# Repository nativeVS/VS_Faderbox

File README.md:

# VS_Faderbox

A small Teensy based MIDI Faderbox;  
built around [ttapa's Control Surface Library](https://github.com/tttapa/Control-Surface)

## Overview

This project was born out of the desire of having a small MIDI fader controller to ease in the work with orchestral libraries.
  
The MIDI Channel and Fader Assignment can be changed via MIDI System Exclusive messages (described in more detail below).
I have written a (low quality) program that lets you quickly generate a SysEx file should you wish to avoid doing it the fun way (link below or [here](https://github.com/nativeVS/VS_SysEx_Generator)).
In addition new for version 5 there is an editor software (link below or [here](https://github.com/nativeVS/VS_Faderbox_Editor)) which is a simple Electron built application using WebMIDI, heavily inspired by the nakedboards editor.
  
On the PCB there is the provision to add 4 extra potentiometers with pull down resistors (eg. for external expression pedals or similar);
more info in the DIY Notes section.
  
### Links

* [ttapa's Control Surface Library](https://github.com/tttapa/Control-Surface)
* [SysEx Generator](https://github.com/nativeVS/VS_SysEx_Generator)
* [Editor](https://github.com/nativeVS/VS_Faderbox_Editor)
* [nakedboards](https://nakedboards.org/)

#### Contents of the sub-directories are as follows
* VS_Faderbox - Teensyduino Sketch
* CAD Files - Full KiCad Project directory for PCB & AutoCAD files for physical box.

## SysEx Format

Channel and Fader Reassignment SysEx Format:
```
F0 [id] [id] [id] [dI] [s1] [s2] [cc] [f0] [f1] [f2] [f3] xx F7
```
With manufacturer ID (`[id] [id] [id]`), device id (`[dI]`) and sub ids #1 & #2 (`[s1] [s2]` which correspond to model number and version number for this device);
the Checksum (xx) includes the entire SysEx message (i.e. starting with the device ID) and should add up to `FF` with all preceding elements.
The Device ID is in the normal version fixed to 0x01.
  
Thus the SysEx string for the default assignment is as follows:
```
F0 00 21 57 01 02 05 01 01 0B 15 14 40 F7
```
To request the current Channel and Fader assignment the box responds to the following SysEx:
```
F0 [id] [id] [id] [dI] [s1] [s2] 0x11 xx F7
```
This will trigger the following response:
```
F0 [id] [id] [id] [dI] 0x00 [s2] [cc] [f0] [f1] [f2] [f3] xx F7
```

It will respond to the standard SysEx ID Requests:
```
F0 7E 01 06 01 F7 (device id 01) or
F0 7E 7F 06 01 F7 (ignore device id)
```
SysEx ID Request Reply:
```
F0 7E 01 06 02 [id] [id] [id] 01 01 00 02 00 00 00 05 F7
                              |   | |   | |---------- Software Version No: v5
                              |   | |---- Model Number: 00 02
                              |---- Family Code: 01 01
```
  
## DIY Notes

todo: add more detail
  
This sketch was designed for a Teensy LC and might not work correctly on lower spec boards.
  
#### Expansion Notes

There is provision for a 6 pin header on the PCB, which connects to V+ (3V3), GND and Analogue Inputs A4, A5, A6 & A7.  

As a general note, I would recommend using Mappingfunctions for any external potentiometers (many expression pedals not having the full resistor range available) as can be found in the [following example](https://github.com/tttapa/Control-Surface/blob/master/examples/1.%20MIDI%20Output/1.%20Potentiometers%20%26%20Faders/CCPotentiometer-Map/CCPotentiometer-Map.ino) part of the Control Surface Library.  

If you are unsure how the general sketch works, I would highly recommend hardcoding MIDI CC and Channel values for any edits.

nativeVS - 2021

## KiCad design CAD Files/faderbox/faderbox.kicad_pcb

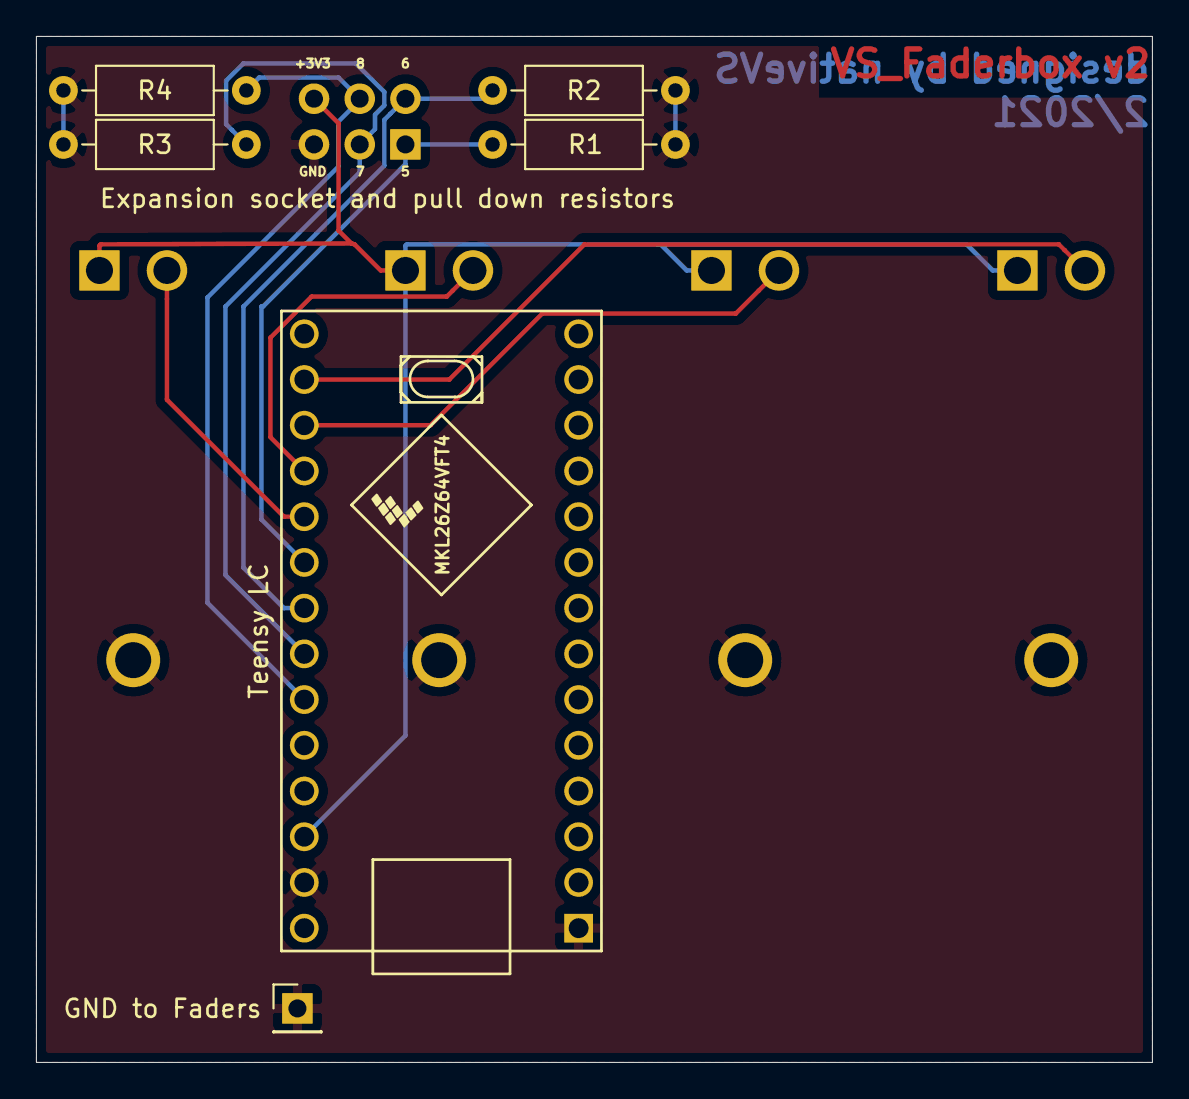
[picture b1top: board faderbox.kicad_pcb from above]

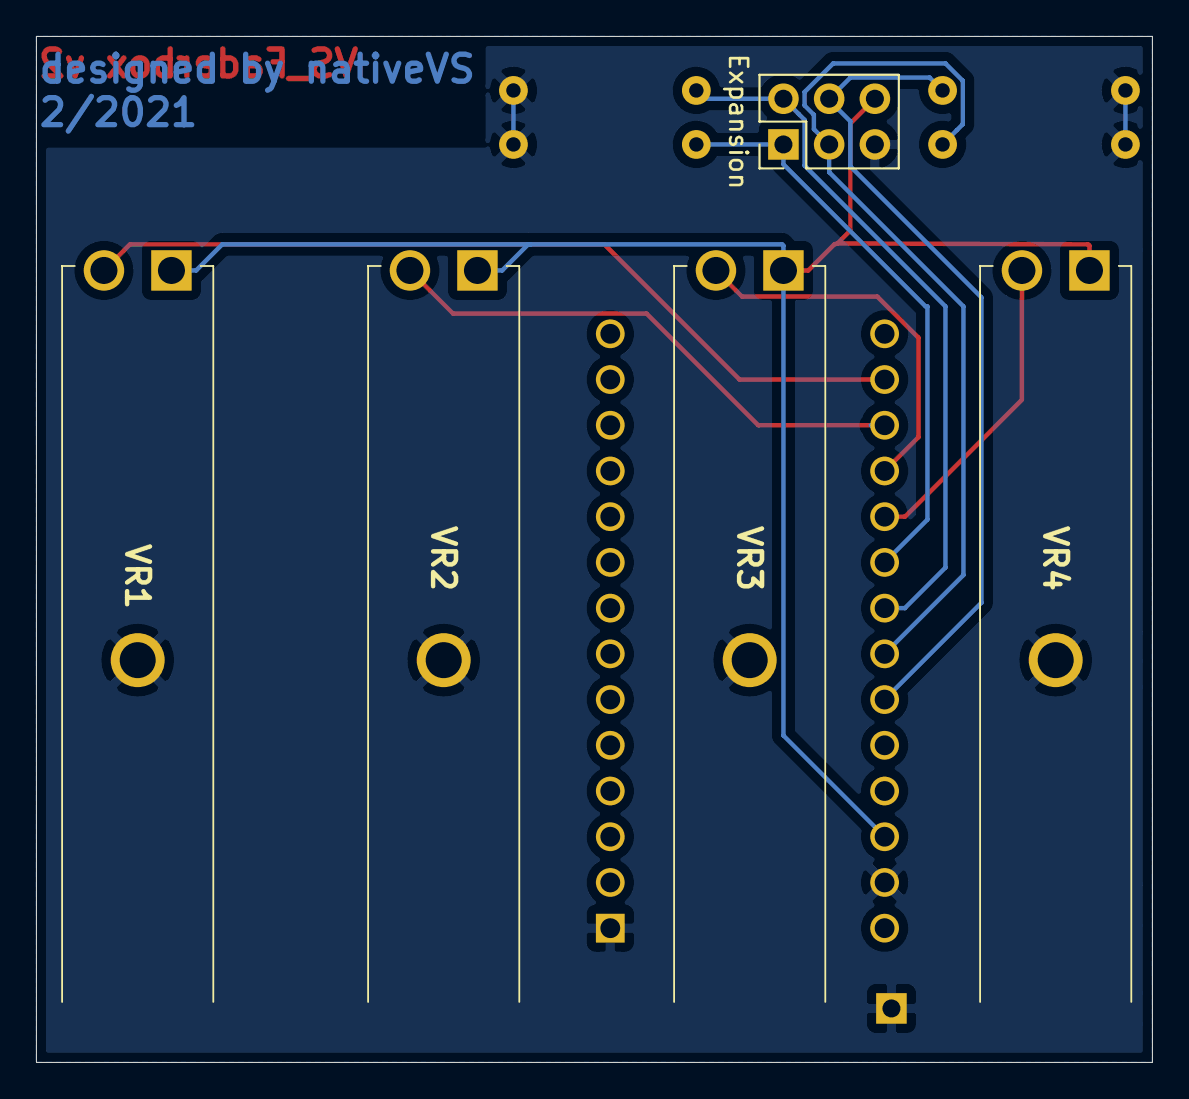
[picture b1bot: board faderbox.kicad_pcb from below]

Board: 2 copper layers, 62.0 x 57.0 mm, 11 parts (5 on the bottom side), 10 nets.

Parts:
Expansion: exp; PinHeader_2x03_P2.54mm_Vertical
GND to Faders: GND to Faders; PinHeader_1x01_P2.54mm_Vertical
R1, R2, R3, R4: 1M; R_Axial_DIN0207_L6.3mm_D2.5mm_P10.16mm_Horizontal
Teensy LC: Teensy-LC; Teensy_LC-reduced
VR1, VR2, VR3, VR4: 10k; RSA0N11S9A0K-half

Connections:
GND: Expansion.5, GND to Faders.1, R1.1, R2.1, R3.1, R4.1, Teensy LC.1, Teensy LC.32, VR1.MH2, VR2.MH2, VR3.MH2, VR4.MH2
unnamed: Expansion.1, R1.2, Teensy LC.25
unnamed: Expansion.2, R2.2, Teensy LC.26
unnamed: Expansion.3, R3.2, Teensy LC.27
unnamed: Expansion.4, R4.2, Teensy LC.28
unnamed: Expansion.6, Teensy LC.31, VR1.1, VR2.1, VR3.1, VR4.1
unnamed: Teensy LC.21, VR1.2
unnamed: Teensy LC.22, VR2.2
unnamed: Teensy LC.23, VR3.2
unnamed: Teensy LC.24, VR4.2

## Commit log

2021-04-03 Add files via upload
    Update to Version 5
2021-04-03 Update README.md
    updated to version 5
